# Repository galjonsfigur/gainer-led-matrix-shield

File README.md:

## GAINER LED Matrix shield PCB and schematics

A simple shield for GAINER I/O board to connect a 8x8 LED Matrix. Single-sided PCB designed in KiCad with large 1206 SMD components. Contents:

- `img/`: Folder with images of the board and connected LED Matrix.
- `schematics.pdf` - Connection diagram exported from KiCad.
- Rest of the files: KiCad design files.

#### Warning
There is a little error in design - spacing between pin headers of GAINER board is too small so female pin headers have to be bent to fit. This shouldn't be an issue if the board is manufactured in very small quantity.

#### License
[CERN Open Hardware Licence](LICENSE)

Author: galion (galion at sdf org)

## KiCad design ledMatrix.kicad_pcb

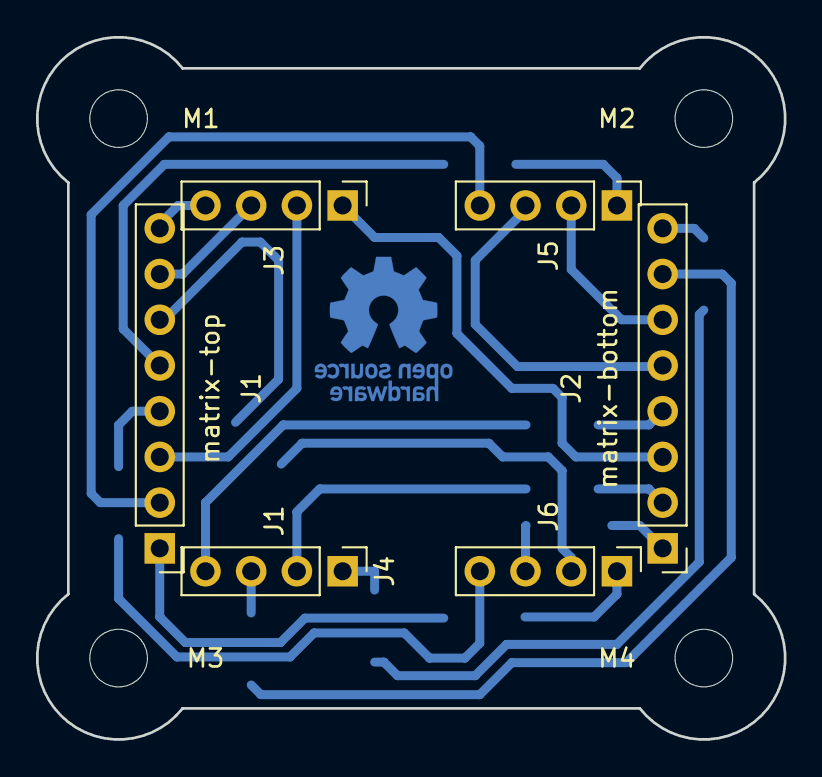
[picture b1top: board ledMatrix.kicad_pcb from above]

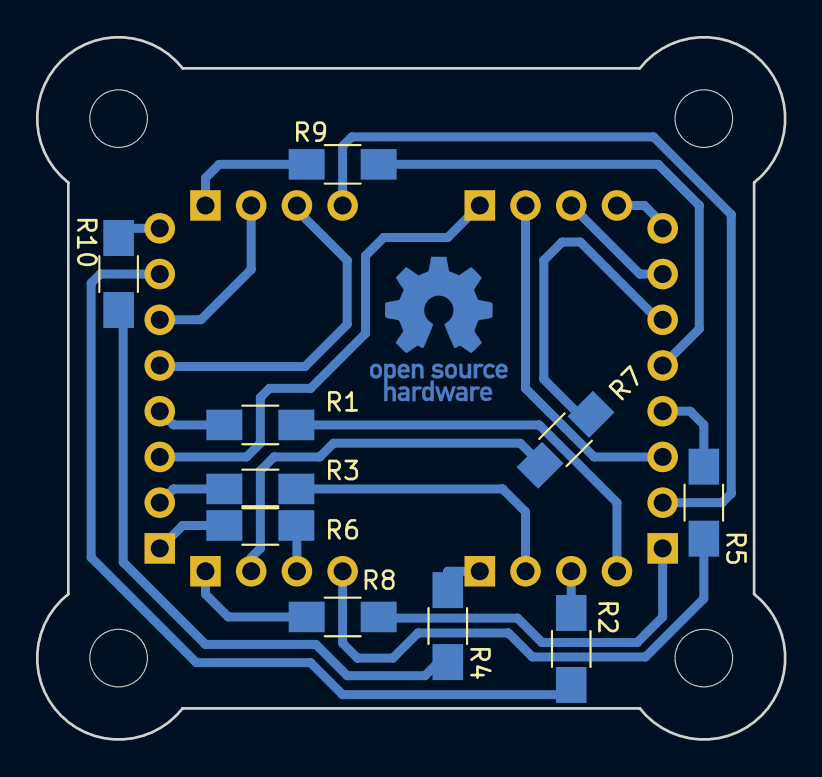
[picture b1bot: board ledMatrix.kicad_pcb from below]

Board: 2 copper layers, 41.5 x 39.0 mm, 21 parts (11 on the bottom side), 26 nets.

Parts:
D1: Logo; OSHW-Logo_7.5x8mm_Copper
J1: matrix-top; Pin_Header_Straight_1x08_Pitch2.54mm
J2: matrix-bottom; Pin_Header_Straight_1x08_Pitch2.54mm
J3: din; Pin_Header_Straight_1x04_Pitch2.54mm
J4: dout; Pin_Header_Straight_1x04_Pitch2.54mm
J5: ain; Pin_Header_Straight_1x04_Pitch2.54mm
J6: aout; Pin_Header_Straight_1x04_Pitch2.54mm
M1: M1; MountingHole_3.2mm_M3
M2: M2; MountingHole_3.2mm_M3
M3: M3; MountingHole_3.2mm_M3
M4: M4; MountingHole_3.2mm_M3
R1, R2, R3, R4, R5, R6, R7, R8: 100; R_1206_HandSoldering
R9, R10: 0; R_1206_HandSoldering

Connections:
unnamed: J1.1, R8.2
unnamed: J1.2, J5.4
unnamed: J1.3, J3.2
unnamed: J1.4, R5.2
unnamed: J1.5, R9.2
unnamed: J1.6, R7.2
unnamed: J1.7, J3.3
unnamed: J1.8, J3.4
unnamed: J2.1, R6.2
unnamed: J2.2, R3.2
unnamed: J2.3, J3.1
unnamed: J2.4, R1.2
unnamed: J2.5, J5.3
unnamed: J2.6, J5.2
unnamed: J2.7, R2.2
unnamed: J2.8, R10.2
unnamed: J4.1, R4.1
unnamed: J4.2, R3.1
unnamed: J4.3, R2.1
unnamed: J4.4, R1.1
unnamed: J5.1, R9.1
unnamed: J6.1, R8.1
unnamed: J6.2, R7.1
unnamed: J6.3, R6.1
unnamed: J6.4, R5.1
unnamed: R4.2, R10.1

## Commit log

2018-12-31 Added LICENSE file and README note
2018-12-31 Added images
2018-12-31 Fix board image
